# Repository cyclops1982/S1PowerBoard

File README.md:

# S1 PowerBoard

Simple board that allows for USB or S1 lipo battery input.
Uses solar panel to charge and has power-path to make sure the 3v3 output is working accordingly.

## Schema

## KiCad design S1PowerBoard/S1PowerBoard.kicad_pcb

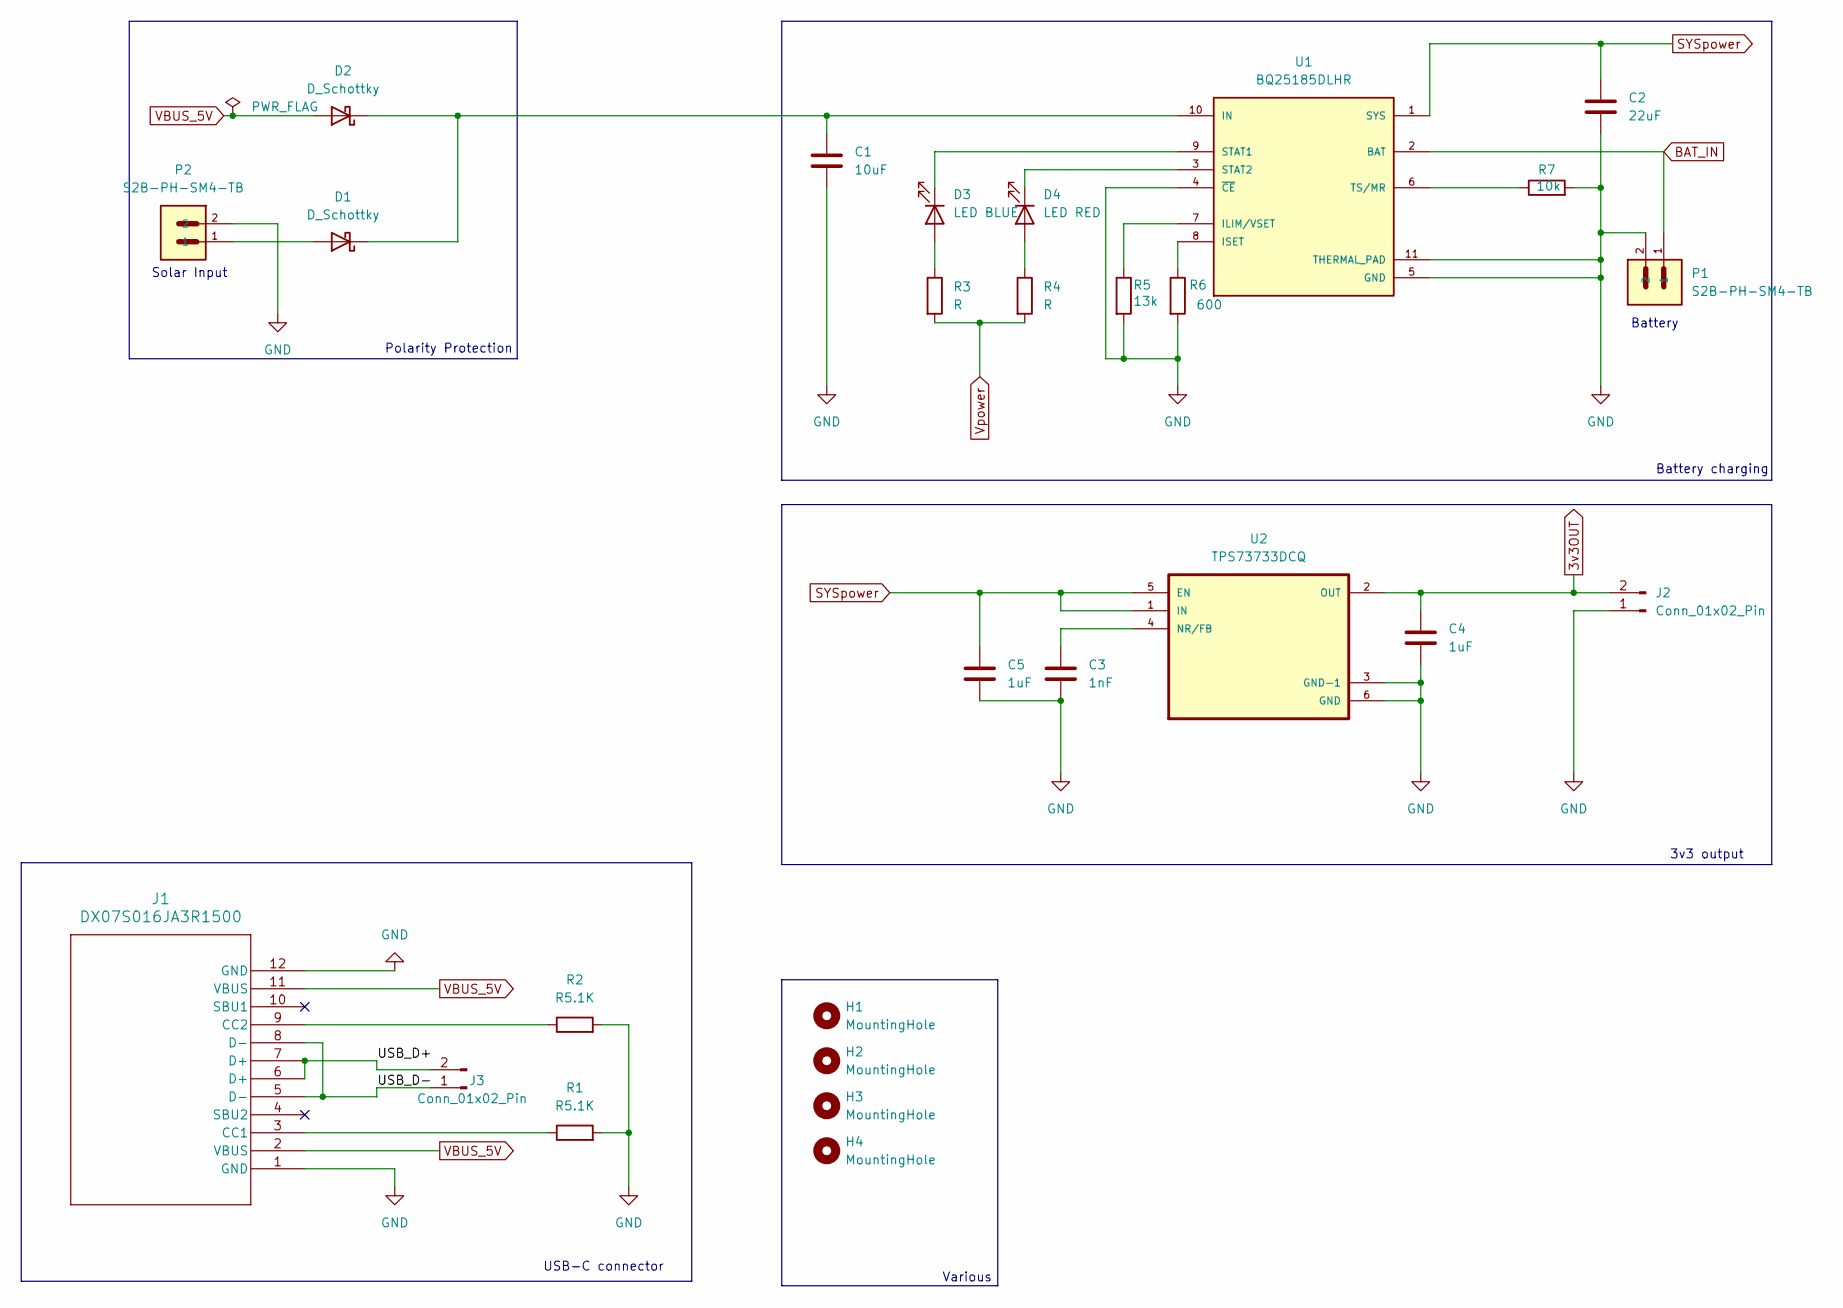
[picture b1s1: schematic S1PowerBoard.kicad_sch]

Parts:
C1: 10uF; C_1206_3216Metric_Pad1.33x1.80mm_HandSolder
C2: 22uF; C_1206_3216Metric_Pad1.33x1.80mm_HandSolder
C3: 1nF; C_1206_3216Metric_Pad1.33x1.80mm_HandSolder
C4, C5: 1uF; C_1206_3216Metric_Pad1.33x1.80mm_HandSolder
D1, D2: D_Schottky; D_1206_3216Metric_Pad1.42x1.75mm_HandSolder
D3: LED BLUE; LED_1206_3216Metric_Pad1.42x1.75mm_HandSolder
D4: LED RED; LED_1206_3216Metric_Pad1.42x1.75mm_HandSolder
H1, H2, H3, H4: MountingHole; MountingHole_2.7mm_M2.5_Pad
J1: DX07S016JA3R1500; CONN12_DX07S_JAE
J2, J3: Conn_01x02_Pin; PinHeader_1x02_P2.54mm_Vertical
P1, P2: S2B-PH-SM4-TB; JST_S2B-PH-SM4-TB
R1, R2: R5.1K; R_1206_3216Metric_Pad1.30x1.75mm_HandSolder
R3, R4: R; R_1206_3216Metric_Pad1.30x1.75mm_HandSolder
R5: 13k; R_1206_3216Metric_Pad1.30x1.75mm_HandSolder
R6: 600; R_1206_3216Metric_Pad1.30x1.75mm_HandSolder
R7: 10k; R_1206_3216Metric_Pad1.30x1.75mm_HandSolder
U1: BQ25185DLHR; IC_BQ25185DLHR; PARTREV OCTOBER 2023
U2: TPS73733DCQ; SOT-223-6

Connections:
3v3OUT: C4.1, J2.2, U2.2 (OUT)
/USB_D+: J1.6 (D+), J1.7 (D+), J3.2
/USB_D-: J1.5 (D-), J1.8 (D-), J3.1
BAT_IN: P1.1, U1.2 (BAT)
GND: C1.2, C2.2, C3.2, C4.2, C5.2, J1.1 (GND), J1.12 (GND), J2.1, P1.2, P2.2, R1.2, R2.2, R5.2, R6.2, R7.2, U1.4 (~CE), U1.5 (GND), U1.11 (THERMAL_PAD), U2.3 (GND-1), U2.6 (GND)
unnamed: D1.2 (A), P2.1
unnamed: C1.1, D1.1 (K), D2.1 (K), U1.10 (IN)
unnamed: D3.2 (A), R3.1
unnamed: D3.1 (K), U1.9 (STAT1)
unnamed: D4.2 (A), R4.1
unnamed: D4.1 (K), U1.3 (STAT2)
unnamed: J1.3 (CC1), R1.1
unnamed: J1.9 (CC2), R2.1
unnamed: R5.1, U1.7 (ILIM/VSET)
unnamed: R6.1, U1.8 (ISET)
unnamed: R7.1, U1.6 (TS/MR)
unnamed: C3.1, U2.4 (NR/FB)
SYSpower: C2.1, C5.1, U1.1 (SYS), U2.1 (IN), U2.5 (EN)
VBUS_5V: D2.2 (A), J1.2 (VBUS), J1.11 (VBUS)
Vpower: R3.2, R4.2

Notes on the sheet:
Battery
3v3 output
Polarity Protection
Solar Input
Various
Battery charging
USB-C connector

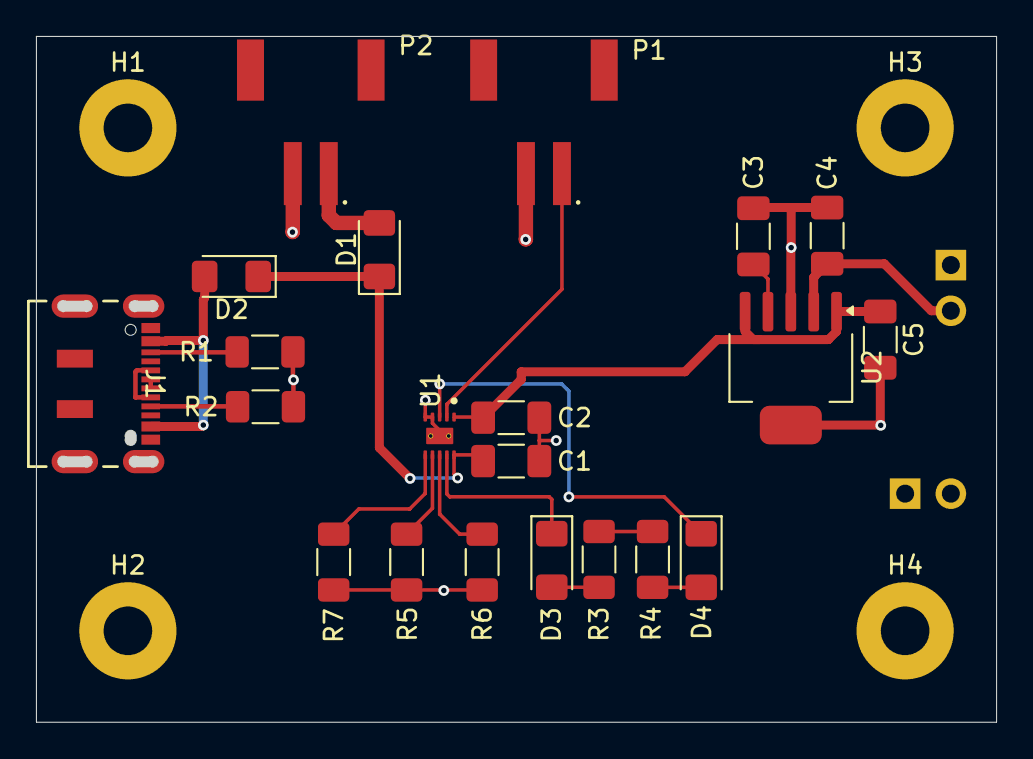
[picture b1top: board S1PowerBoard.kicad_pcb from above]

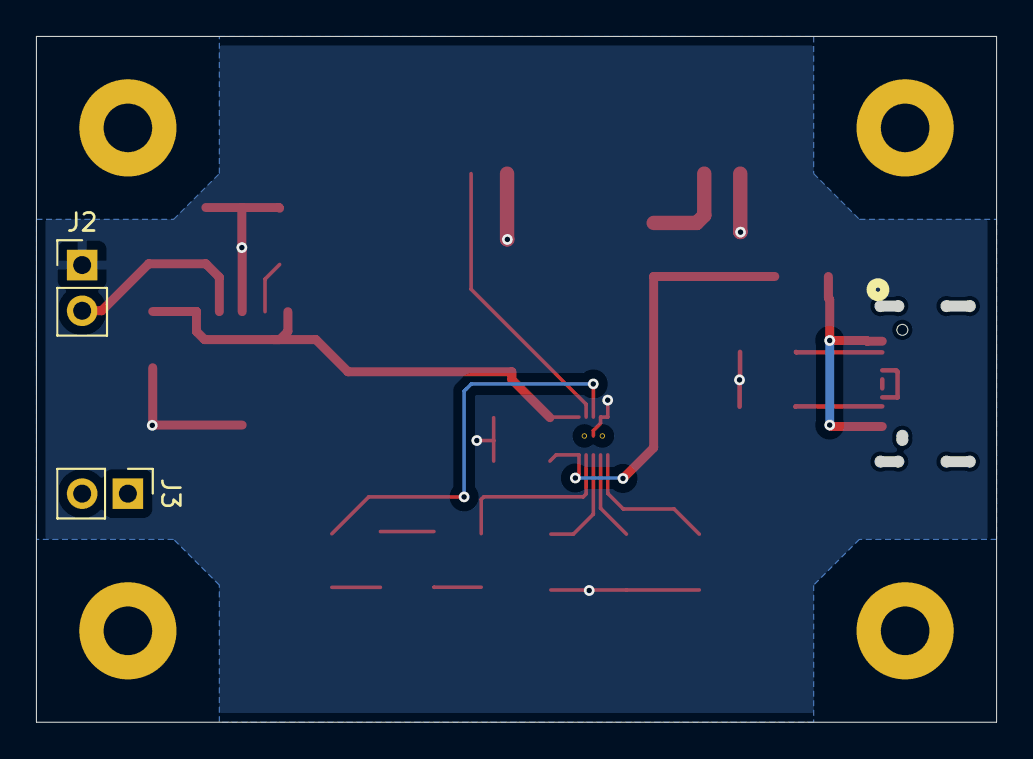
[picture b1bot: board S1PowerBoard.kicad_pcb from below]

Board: 2 copper layers, 53.3 x 38.1 mm, 27 parts (2 on the bottom side), 20 nets.

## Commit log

2026-01-11 Initial version of board
2026-01-11 Add readme
2026-01-11 Add USB-C connector stuff
2026-01-11 Add screenshot of schema
2026-01-11 Add initial pcb layout
